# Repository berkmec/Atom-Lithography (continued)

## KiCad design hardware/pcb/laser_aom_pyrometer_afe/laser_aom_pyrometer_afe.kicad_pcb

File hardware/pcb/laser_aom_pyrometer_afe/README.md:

# Laser `80–200 MHz` AOM RF VCA, `10 µs` 2-Color Pyrometer TIA, `1.0 ms` Integrator & `< 0.1 ms` Crowbar PCB

**BOM Coverage:** `S5.5-03`, `S5.5-01`, `S5.5-04`, `S5.3-03` (interfacing `rtl/machine_ctrl/aom_pid_ctrl.v` and `safety_interlock_1oo2d`)  
**Epistemic Status:** `M0/M1_DESIGN_ONLY` — `no_lab_measurement=true`, `no_physical_fab=true`, `iec61508_certified=false`, `semi_s2_certified=false`. All active semiconductors are `{Aday-COTS}` candidate parts.

## 1. Board Summary & Strict KiCad 8 EDA Verification

| Parameter | Value / Measured Result | Requirement / Spec | Status |
| :--- | :--- | :--- | :---: |
| Stackup & Geometry | 4-layer Rogers RO4350B (`ε_r=3.48`, `0.254 mm` outer RF/TIA layers) + Isola FR408HR (`0.800 mm` core), `185 × 125 mm` | 4L Rogers/FR4 mixed-signal PCB | **PASS** |
| Physical Routing & Connectivity | **`63 / 63` multi-pin nets routed (`100%`)**, `835` segments, `221` vias, **`0` unrouted**, **`0` unconnected**, **`0` dangling** | 100% pad-to-pad routed Union-Find DRC | **PASS** |
| Schematic / PCB Netlist | `75` components, `63` nets, `2` closed 3D via-tied `AGND` TIA guard cages (`connect_guard_ring`), `2` `In1/In2` TIA copper keepouts | Strict S-expr + SCH↔PCB parity | **PASS** |
| ERC / DRC Errors | **`0` ERC / `0` DRC** | `0 / 0` | **PASS** |
| Controlled-Impedance `50 Ω` RF Chain (`14` checks) | `Z0 = 50.00 Ω` (`w = 0.5429 mm`, `0.001%` max error across `80–200 MHz` AOM RF path) | `50 Ω ± 5%` | **PASS** |

## 2. Architecture

- **2-Color Fast Pyrometer TIA (`S5.5-03`, `S5.3-03`, `900–1700 K`, `τ_rise ≤ 10 µs`):**
  - InGaAs `1550 nm` (`Hamamatsu G12180-010A`, `OPA657NB`, `R_f = 100 kΩ`, `C_f = 12 pF`) + Si `850 nm` (`Hamamatsu S5971`, `OPA657NB`, `R_f = 200 kΩ`, `C_f = 6.0 pF`) with `F.Cu` guard rings and `In1/In2` copper keepouts feeding dual `ADS8860` 16-bit `1 MS/s` ADCs.
  - Dedicated `TLV3501` hardware over-temperature comparator (`T ≥ 1687 K` Si melt backup) hardwired directly into the local crowbar gate.
- **Inline `1.0 ms` Photodiode Pulse-Energy Integrator (`S5.5-03`):** `Hamamatsu S1223-01` pickoff photodiode → `OPA140` JFET Miller integrator (`C_INT = 100 nF` C0G `±0.5%`, `ADG1211` low-charge-injection reset switch) → `ADS8860` 16-bit ADC + `50 Ω` SMA diagnostic tap.
- **`80–200 MHz` AOM RF VCA Stage (`S5.5-01`, `aom_pid_ctrl.v`):** `AD5541A` 16-bit `100 kHz` SPI DAC + `LT6655B-2.5` ref → `ADA4898-1` VCA driver (`[0.65, 1.40]` gain) → `AD8367` `50 Ω` VCA → `ADG901/HMC547A` `< 15 ns` absorptive RF kill switch → `ADL5602` `50 Ω` output amplifier.
- **`< 0.1 ms` Hardware Crowbar (`S5.5-04`, wired directly to `safety_interlock_1oo2d`):** Dual `ACPL-072L` `< 60 ns` optocouplers (`SAFE_LASER_EN_A`, `SAFE_LASER_EN_B`) in hardware `1oo2` AND gating: (1) `2N7002` VCA zero-clamp, (2) RF kill switch, and (3) series dual-MOSFET `SI2302` `24 V` diode-laser enable cutoff.

## 3. Live `ngspice-47` & Independent MNA Results (`laser_pyro_tia_aom.cir`)

| Metric | `ngspice-47` Measured | Independent Python MNA Ref | Target / Spec | Status |
| :--- | :---: | :---: | :---: | :---: |
| InGaAs `1550 nm` TIA `10–90%` Rise Time | **`2.636 µs`** (`f_-3dB = 132.65 kHz`) | MNA `Z_dc = 99,996.16 Ω` (`0.00004%` diff) | `τ_rise < 10 µs` | **PASS** |
| Si `850 nm` TIA `10–90%` Rise Time | **`2.636 µs`** (`f_-3dB = 132.65 kHz`) | MNA `Z_dc = 199,992.32 Ω` | `τ_rise < 10 µs` | **PASS** |
| `1.0 ms` Pulse-Energy Integrator `2×` Sweep | `1× = 0.999993 V`, `2× = 1.999990 V` (**`0.00001%`** lin err, `0.000 mV` reset) | Ideal `2.00000×` | `< 1.0%` (`±1.5%` BOM) | **PASS** |
| AOM VCA Gain Modulation & RF Flatness | `1.40 / 0.65` ratio **`2.1538`**, `80–200 MHz` flatness **`0.0008 dB`** | Exact `2.15385` | `[0.65, 1.40]`, `< 0.5 dB` | **PASS** |
| Hardware Crowbar Cutoff (`SAFE_LASER_EN_A = 0`) | VCA clamp **`0.273 µs`**, `24 V` Diode-EN **`4.870 µs`** (`23.93 V → 0.12 mV`) | — | `< 50 µs` (`<< 0.1 ms`) | **PASS** |

## 4. Reproducibility

```bash
PYTHONPATH=.:src python -B hardware/pcb/laser_aom_pyrometer_afe/build_laser_aom_pyrometer_afe.py
PYTHONPATH=.:src pytest tests/test_pcb_hv_laser_safety.py -v -p no:cacheprovider
```

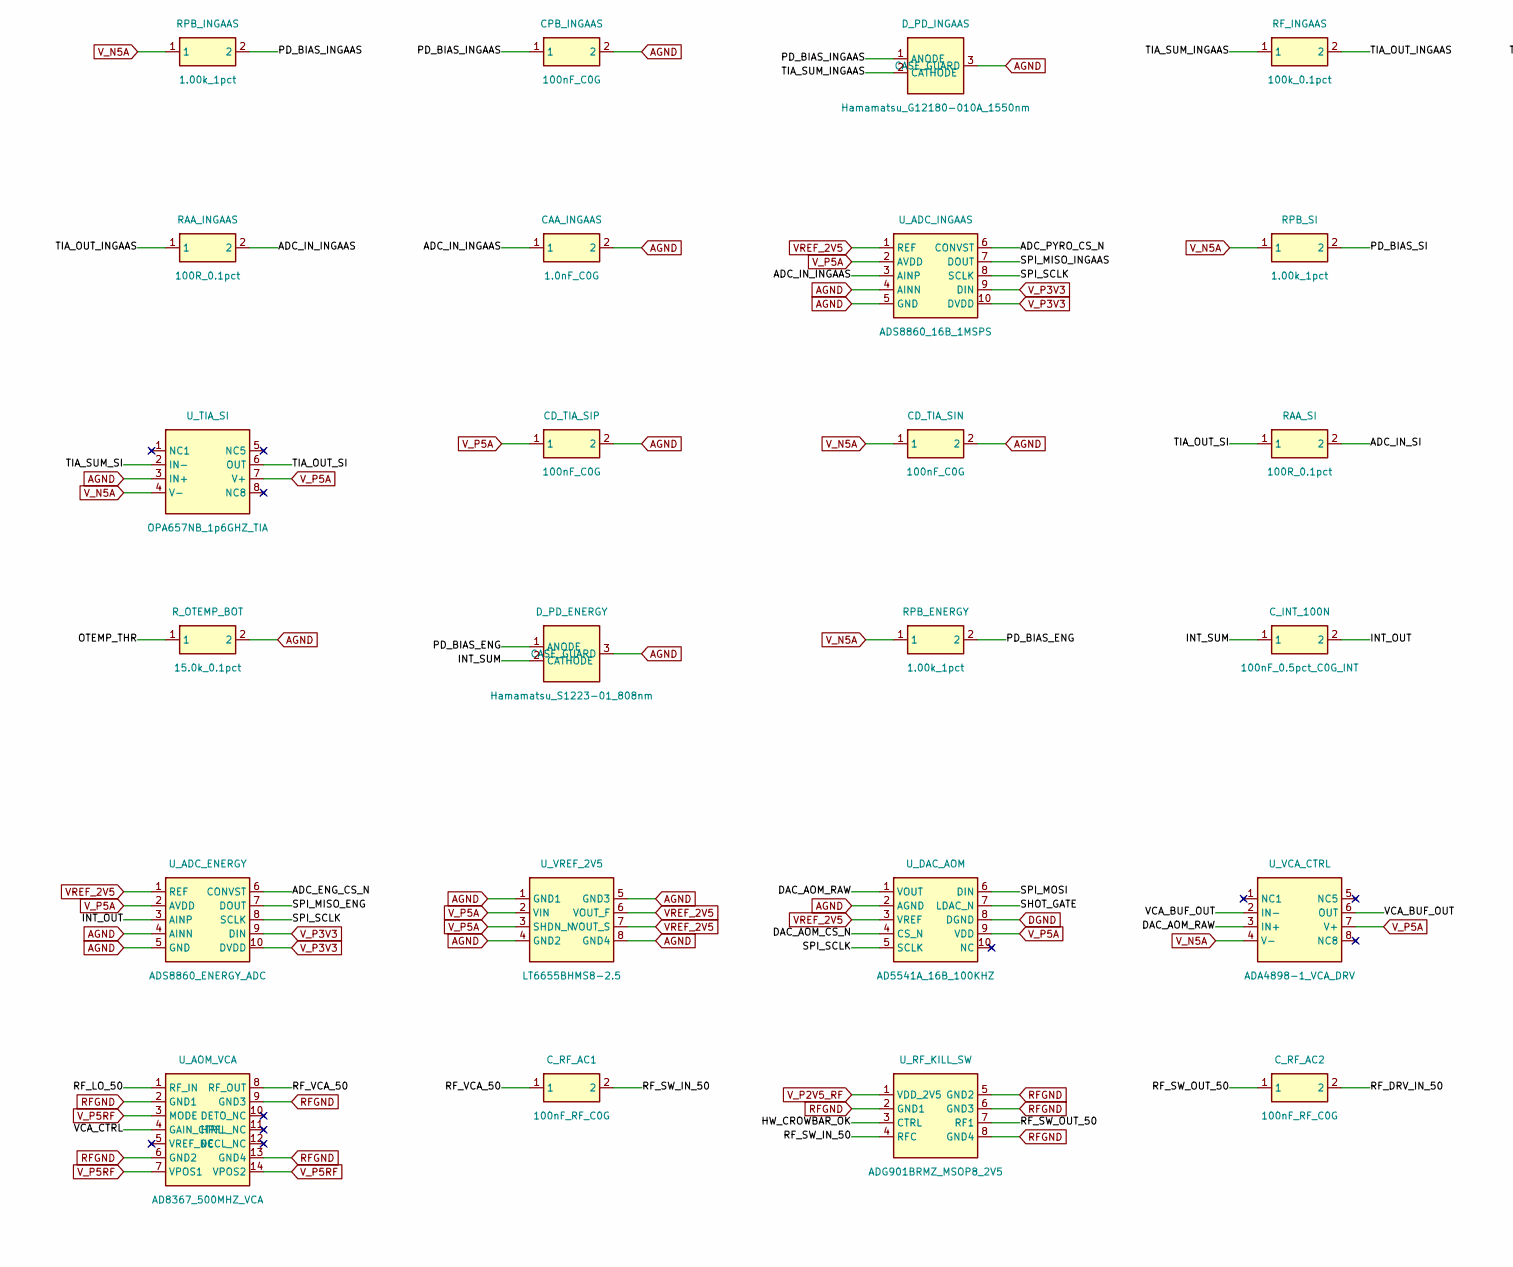
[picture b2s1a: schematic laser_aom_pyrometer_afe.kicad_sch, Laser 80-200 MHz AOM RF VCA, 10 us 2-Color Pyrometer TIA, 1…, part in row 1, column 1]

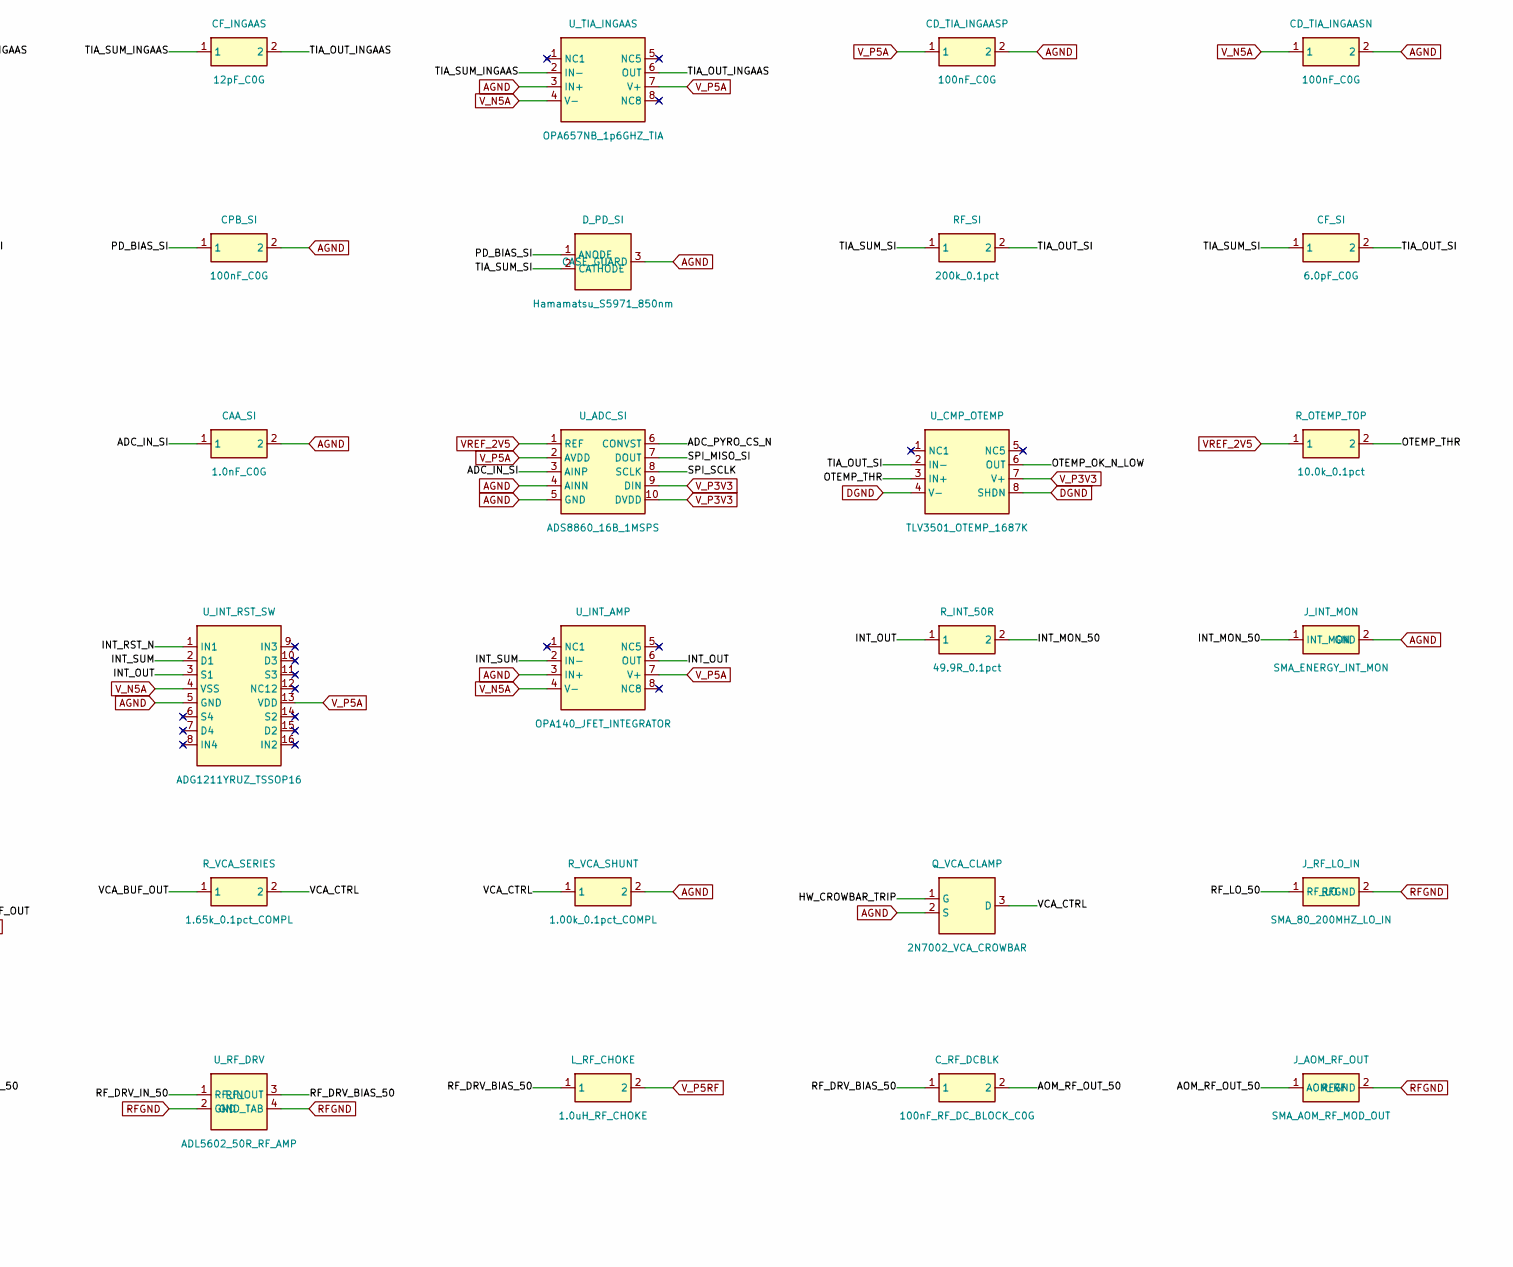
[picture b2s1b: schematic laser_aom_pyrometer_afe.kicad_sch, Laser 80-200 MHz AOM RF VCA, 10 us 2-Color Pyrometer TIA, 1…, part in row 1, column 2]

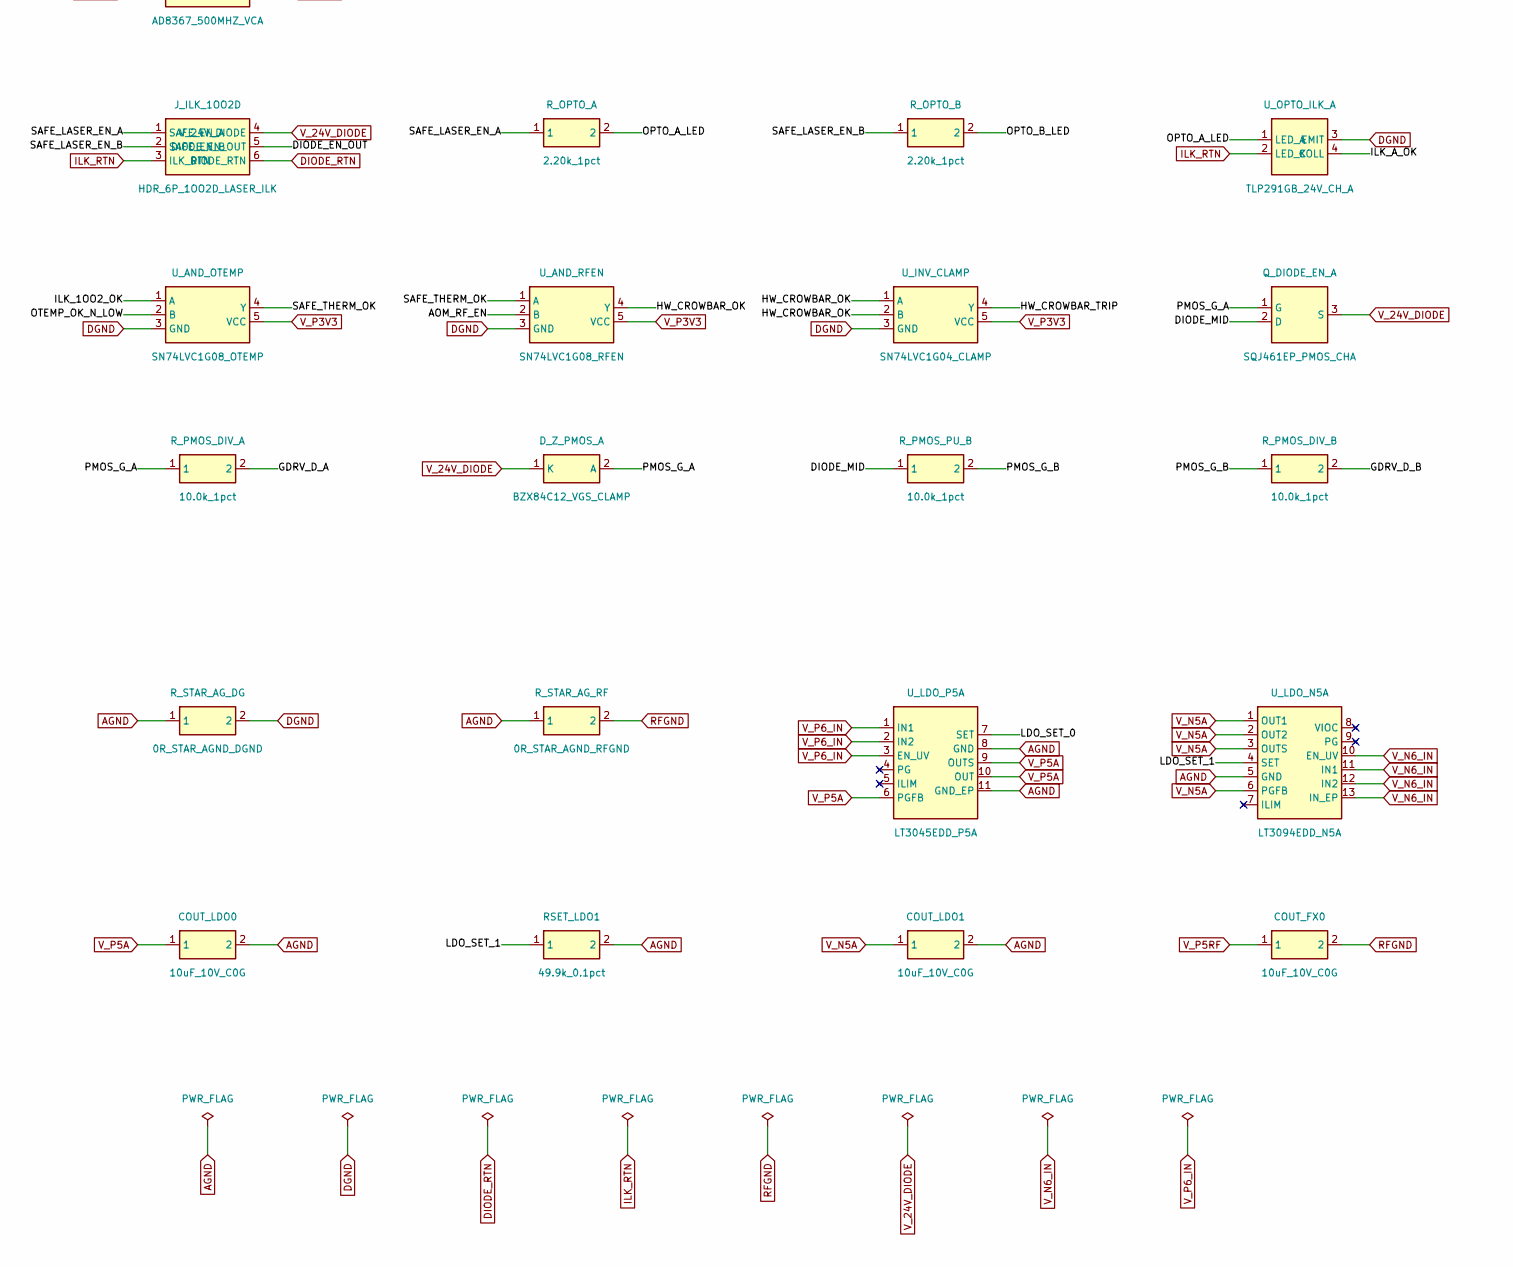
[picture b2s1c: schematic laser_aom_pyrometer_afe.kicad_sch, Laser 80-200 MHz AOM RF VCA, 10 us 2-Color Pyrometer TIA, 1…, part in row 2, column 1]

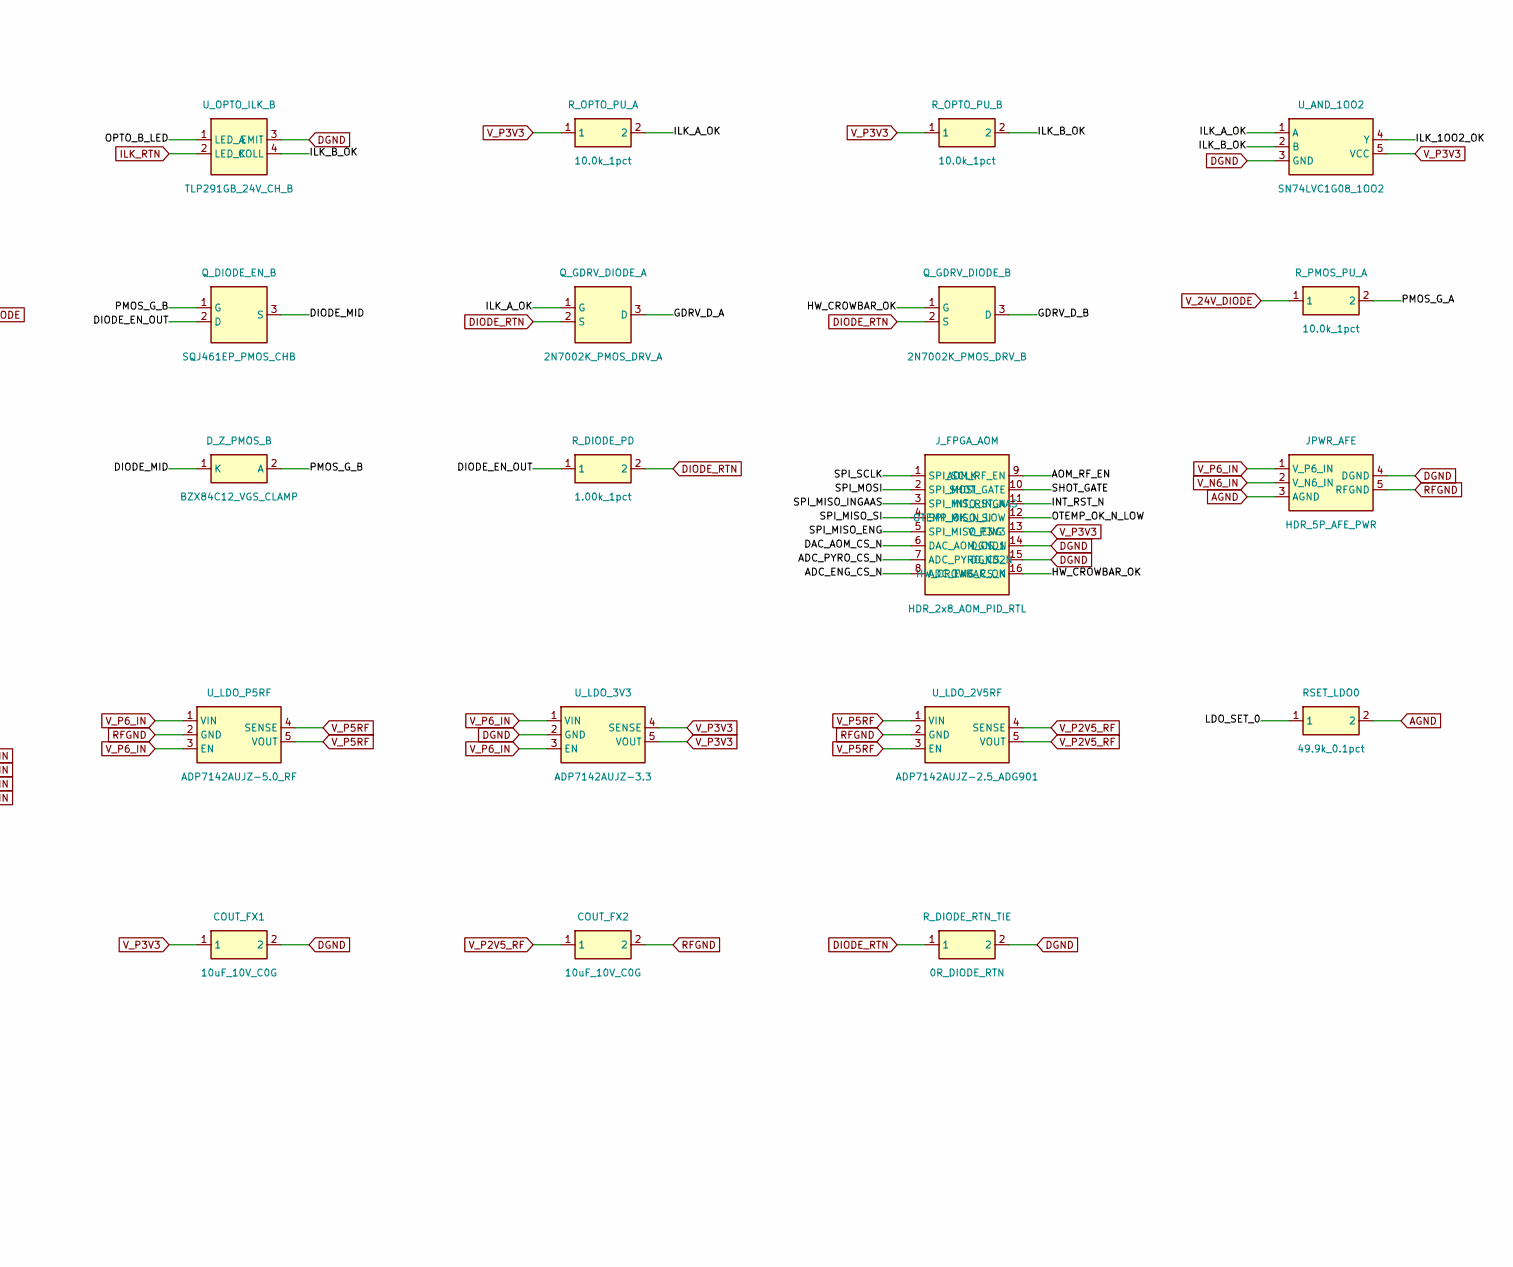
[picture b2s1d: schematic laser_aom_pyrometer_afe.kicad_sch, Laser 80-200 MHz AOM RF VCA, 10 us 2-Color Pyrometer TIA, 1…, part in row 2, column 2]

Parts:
CAA_INGAAS: 1.0nF_C0G; C_0603_1608Metric; MPN 1.0nF_C0G
CAA_SI: 1.0nF_C0G; C_0603_1608Metric; MPN 1.0nF_C0G
CD_TIA_INGAASN: 100nF_C0G; C_0603_1608Metric; MPN 100nF_C0G
CD_TIA_INGAASP: 100nF_C0G; C_0603_1608Metric; MPN 100nF_C0G
CD_TIA_SIN: 100nF_C0G; C_0603_1608Metric; MPN 100nF_C0G
CD_TIA_SIP: 100nF_C0G; C_0603_1608Metric; MPN 100nF_C0G
CF_INGAAS: 12pF_C0G; C_0603_1608Metric; MPN 12pF_C0G
CF_SI: 6.0pF_C0G; C_0603_1608Metric; MPN 6.0pF_C0G
COUT_FX0, COUT_FX1, COUT_FX2: 10uF_10V_C0G; C_0603_1608Metric; MPN 10uF_10V_C0G
COUT_LDO0, COUT_LDO1: 10uF_10V_C0G; C_0603_1608Metric; MPN 10uF_10V_C0G
CPB_INGAAS: 100nF_C0G; C_0603_1608Metric; MPN 100nF_C0G
CPB_SI: 100nF_C0G; C_0603_1608Metric; MPN 100nF_C0G
C_INT_100N: 100nF_0.5pct_C0G_INT; C_1206_3216Metric; MPN TDK_C3216C0G1H104J
C_RF_AC1, C_RF_AC2: 100nF_RF_C0G; C_0603_1608Metric; MPN 100nF_RF_C0G
C_RF_DCBLK: 100nF_RF_DC_BLOCK_C0G; C_0603_1608Metric; MPN 100nF_RF_DC_BLOCK_C0G
D_PD_ENERGY: Hamamatsu_S1223-01_808nm; TO46_PHOTODIODE_3P; MPN Hamamatsu_S1223-01
D_PD_INGAAS: Hamamatsu_G12180-010A_1550nm; TO46_PHOTODIODE_3P; MPN Hamamatsu_G12180-010A_1550nm
D_PD_SI: Hamamatsu_S5971_850nm; TO46_PHOTODIODE_3P; MPN Hamamatsu_S5971_850nm
D_Z_PMOS_A: BZX84C12_VGS_CLAMP; D_0805_2012Metric; MPN BZX84C12_VGS_CLAMP
D_Z_PMOS_B: BZX84C12_VGS_CLAMP; D_0805_2012Metric; MPN BZX84C12_VGS_CLAMP
JPWR_AFE: HDR_5P_AFE_PWR; HDR_1x5_2.54mm; MPN HDR_5P_AFE_PWR
J_AOM_RF_OUT: SMA_AOM_RF_MOD_OUT; SMA_EdgeMount; MPN SMA_AOM_RF_MOD_OUT
J_FPGA_AOM: HDR_2x8_AOM_PID_RTL; HDR_2x8_2.54mm; MPN HDR_2x8_AOM_PID_RTL
J_ILK_1OO2D: HDR_6P_1OO2D_LASER_ILK; HDR_1x6_2.54mm; MPN HDR_6P_1OO2D_LASER_ILK
J_INT_MON: SMA_ENERGY_INT_MON; SMA_EdgeMount; MPN SMA_ENERGY_INT_MON
J_RF_LO_IN: SMA_80_200MHZ_LO_IN; SMA_EdgeMount; MPN SMA_80_200MHZ_LO_IN
L_RF_CHOKE: 1.0uH_RF_CHOKE; L_0805_2012Metric; MPN 1.0uH_RF_CHOKE
Q_DIODE_EN_A: SQJ461EP_PMOS_CHA; TO-252-2; MPN Vishay_SQJ461EP
Q_DIODE_EN_B: SQJ461EP_PMOS_CHB; TO-252-2; MPN Vishay_SQJ461EP
Q_GDRV_DIODE_A: 2N7002K_PMOS_DRV_A; SOT-23; MPN 2N7002K
Q_GDRV_DIODE_B: 2N7002K_PMOS_DRV_B; SOT-23; MPN 2N7002K
Q_VCA_CLAMP: 2N7002_VCA_CROWBAR; SOT-23; MPN 2N7002K
RAA_INGAAS: 100R_0.1pct; R_0603_1608Metric; MPN 100R_0.1pct
RAA_SI: 100R_0.1pct; R_0603_1608Metric; MPN 100R_0.1pct
RF_INGAAS: 100k_0.1pct; R_0603_1608Metric; MPN 100k_0.1pct
RF_SI: 200k_0.1pct; R_0603_1608Metric; MPN 200k_0.1pct
RPB_ENERGY: 1.00k_1pct; R_0603_1608Metric; MPN 1.00k_1pct
RPB_INGAAS: 1.00k_1pct; R_0603_1608Metric; MPN 1.00k_1pct
RPB_SI: 1.00k_1pct; R_0603_1608Metric; MPN 1.00k_1pct
RSET_LDO0, RSET_LDO1: 49.9k_0.1pct; R_0603_1608Metric; MPN 49.9k_0.1pct
R_DIODE_PD: 1.00k_1pct; R_0805_2012Metric; MPN 1.00k_1pct
R_DIODE_RTN_TIE: 0R_DIODE_RTN; R_0603_1608Metric; MPN 0R_DIODE_RTN
R_INT_50R: 49.9R_0.1pct; R_0603_1608Metric; MPN 49.9R_0.1pct
R_OPTO_A: 2.20k_1pct; R_0805_2012Metric; MPN 2.20k_1pct
R_OPTO_B: 2.20k_1pct; R_0805_2012Metric; MPN 2.20k_1pct
R_OPTO_PU_A: 10.0k_1pct; R_0603_1608Metric; MPN 10.0k_1pct
R_OPTO_PU_B: 10.0k_1pct; R_0603_1608Metric; MPN 10.0k_1pct
R_OTEMP_BOT: 15.0k_0.1pct; R_0603_1608Metric; MPN 15.0k_0.1pct
R_OTEMP_TOP: 10.0k_0.1pct; R_0603_1608Metric; MPN 10.0k_0.1pct
R_PMOS_DIV_A: 10.0k_1pct; R_0603_1608Metric; MPN 10.0k_1pct
R_PMOS_DIV_B: 10.0k_1pct; R_0603_1608Metric; MPN 10.0k_1pct
R_PMOS_PU_A: 10.0k_1pct; R_0603_1608Metric; MPN 10.0k_1pct
R_PMOS_PU_B: 10.0k_1pct; R_0603_1608Metric; MPN 10.0k_1pct
R_STAR_AG_DG: 0R_STAR_AGND_DGND; R_0603_1608Metric; MPN 0R_STAR_AGND_DGND
R_STAR_AG_RF: 0R_STAR_AGND_RFGND; R_0603_1608Metric; MPN 0R_STAR_AGND_RFGND
R_VCA_SERIES: 1.65k_0.1pct_COMPL; R_0603_1608Metric; MPN 1.65k_0.1pct_COMPL
R_VCA_SHUNT: 1.00k_0.1pct_COMPL; R_0603_1608Metric; MPN 1.00k_0.1pct_COMPL
U_ADC_ENERGY: ADS8860_ENERGY_ADC; MSOP-10_3x3mm_P0.5mm; MPN ADS8860IDGK
U_ADC_INGAAS: ADS8860_16B_1MSPS; MSOP-10_3x3mm_P0.5mm; MPN ADS8860IDGK
U_ADC_SI: ADS8860_16B_1MSPS; MSOP-10_3x3mm_P0.5mm; MPN ADS8860IDGK
U_AND_1OO2: SN74LVC1G08_1OO2; SOT-23-5; MPN SN74LVC1G08DBVR
U_AND_OTEMP: SN74LVC1G08_OTEMP; SOT-23-5; MPN SN74LVC1G08DBVR
U_AND_RFEN: SN74LVC1G08_RFEN; SOT-23-5; MPN SN74LVC1G08DBVR
U_AOM_VCA: AD8367_500MHZ_VCA; TSSOP-14_4.4x5mm_P0.65mm; MPN AD8367ARUZ
U_CMP_OTEMP: TLV3501_OTEMP_1687K; SOIC-8_3.9x4.9mm_P1.27mm; MPN TLV3501AID
U_DAC_AOM: AD5541A_16B_100KHZ; MSOP-10_3x3mm_P0.5mm; MPN AD5541ABRMZ
U_INT_AMP: OPA140_JFET_INTEGRATOR; SOIC-8_3.9x4.9mm_P1.27mm; MPN OPA140AID
U_INT_RST_SW: ADG1211YRUZ_TSSOP16; TSSOP-16_4.4x5mm_P0.65mm; MPN ADG1211YRUZ
U_INV_CLAMP: SN74LVC1G04_CLAMP; SOT-23-5; MPN SN74LVC1G04DBVR
U_LDO_2V5RF: ADP7142AUJZ-2.5_ADG901; TSOT-23-5; MPN ADP7142AUJZ-2.5
U_LDO_3V3: ADP7142AUJZ-3.3; TSOT-23-5; MPN ADP7142AUJZ-3.3
U_LDO_N5A: LT3094EDD_N5A; DFN-12-1EP_3x3mm_P0.45mm_EP1.65x2.38mm; MPN LT3094EDD
U_LDO_P5A: LT3045EDD_P5A; DFN-10-1EP_3x3mm_P0.5mm_EP1.55x2.48mm; MPN LT3045EDD
U_LDO_P5RF: ADP7142AUJZ-5.0_RF; TSOT-23-5; MPN ADP7142AUJZ-5.0
U_OPTO_ILK_A: TLP291GB_24V_CH_A; SOP-4_3.8x4.1mm_P2.54mm; MPN TLP291GB
U_OPTO_ILK_B: TLP291GB_24V_CH_B; SOP-4_3.8x4.1mm_P2.54mm; MPN TLP291GB
U_RF_DRV: ADL5602_50R_RF_AMP; SOT89_RF_4P; MPN ADL5602ARKZ
U_RF_KILL_SW: ADG901BRMZ_MSOP8_2V5; MSOP-8_3x3mm_P0.65mm; MPN ADG901BRMZ
U_TIA_INGAAS: OPA657NB_1p6GHZ_TIA; SOIC-8_3.9x4.9mm_P1.27mm; MPN OPA657NB
U_TIA_SI: OPA657NB_1p6GHZ_TIA; SOIC-8_3.9x4.9mm_P1.27mm; MPN OPA657NB
U_VCA_CTRL: ADA4898-1_VCA_DRV; SOIC-8_3.9x4.9mm_P1.27mm; MPN ADA4898-1YRDZ
U_VREF_2V5: LT6655BHMS8-2.5; MSOP-8_3x3mm_P0.65mm; MPN LT6655BHMS8-2.5

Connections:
ADC_ENG_CS_N: J_FPGA_AOM.8 (ADC_ENG_CS_N), U_ADC_ENERGY.6 (CONVST)
ADC_IN_INGAAS: CAA_INGAAS.1, RAA_INGAAS.2, U_ADC_INGAAS.3 (AINP)
ADC_IN_SI: CAA_SI.1, RAA_SI.2, U_ADC_SI.3 (AINP)
ADC_PYRO_CS_N: J_FPGA_AOM.7 (ADC_PYRO_CS_N), U_ADC_INGAAS.6 (CONVST), U_ADC_SI.6 (CONVST)
AGND: CAA_INGAAS.2, CAA_SI.2, CD_TIA_INGAASN.2, CD_TIA_INGAASP.2, CD_TIA_SIN.2, CD_TIA_SIP.2, COUT_LDO0.2, COUT_LDO1.2, CPB_INGAAS.2, CPB_SI.2, D_PD_ENERGY.3 (CASE_GUARD), D_PD_INGAAS.3 (CASE_GUARD), D_PD_SI.3 (CASE_GUARD), JPWR_AFE.3 (AGND), J_INT_MON.2 (GND), Q_VCA_CLAMP.2 (S), RSET_LDO0.2, RSET_LDO1.2, R_OTEMP_BOT.2, R_STAR_AG_DG.1, R_STAR_AG_RF.1, R_VCA_SHUNT.2, U_ADC_ENERGY.4 (AINN), U_ADC_ENERGY.5 (GND), U_ADC_INGAAS.4 (AINN), U_ADC_INGAAS.5 (GND), U_ADC_SI.4 (AINN), U_ADC_SI.5 (GND), U_DAC_AOM.2 (AGND), U_INT_AMP.3 (IN+), U_INT_RST_SW.5 (GND), U_LDO_N5A.5 (GND), U_LDO_P5A.8 (GND), U_LDO_P5A.11 (GND_EP), U_TIA_INGAAS.3 (IN+), U_TIA_SI.3 (IN+), U_VREF_2V5.1 (GND1), U_VREF_2V5.4 (GND2), U_VREF_2V5.5 (GND3), U_VREF_2V5.8 (GND4)
AOM_RF_EN: J_FPGA_AOM.9 (AOM_RF_EN), U_AND_RFEN.2 (B)
AOM_RF_OUT_50: C_RF_DCBLK.2, J_AOM_RF_OUT.1 (AOM_RF)
DAC_AOM_CS_N: J_FPGA_AOM.6 (DAC_AOM_CS_N), U_DAC_AOM.4 (CS_N)
DAC_AOM_RAW: U_DAC_AOM.1 (VOUT), U_VCA_CTRL.3 (IN+)
DGND: COUT_FX1.2, JPWR_AFE.4 (DGND), J_FPGA_AOM.14 (DGND1), J_FPGA_AOM.15 (DGND2), R_DIODE_RTN_TIE.2, R_STAR_AG_DG.2, U_AND_1OO2.3 (GND), U_AND_OTEMP.3 (GND), U_AND_RFEN.3 (GND), U_CMP_OTEMP.4 (V-), U_CMP_OTEMP.8 (SHDN), U_DAC_AOM.8 (DGND), U_INV_CLAMP.3 (GND), U_LDO_3V3.2 (GND), U_OPTO_ILK_A.3 (EMIT), U_OPTO_ILK_B.3 (EMIT)
DIODE_EN_OUT: J_ILK_1OO2D.5 (DIODE_EN_OUT), Q_DIODE_EN_B.2 (D), R_DIODE_PD.1
DIODE_MID: D_Z_PMOS_B.1 (K), Q_DIODE_EN_A.2 (D), Q_DIODE_EN_B.3 (S), R_PMOS_PU_B.1
DIODE_RTN: J_ILK_1OO2D.6 (DIODE_RTN), Q_GDRV_DIODE_A.2 (S), Q_GDRV_DIODE_B.2 (S), R_DIODE_PD.2, R_DIODE_RTN_TIE.1
GDRV_D_A: Q_GDRV_DIODE_A.3 (D), R_PMOS_DIV_A.2
GDRV_D_B: Q_GDRV_DIODE_B.3 (D), R_PMOS_DIV_B.2
HW_CROWBAR_OK: J_FPGA_AOM.16 (HW_CROWBAR_OK), Q_GDRV_DIODE_B.1 (G), U_AND_RFEN.4 (Y), U_INV_CLAMP.1 (A), U_INV_CLAMP.2 (B), U_RF_KILL_SW.3 (CTRL)
HW_CROWBAR_TRIP: Q_VCA_CLAMP.1 (G), U_INV_CLAMP.4 (Y)
ILK_1OO2_OK: U_AND_1OO2.4 (Y), U_AND_OTEMP.1 (A)
ILK_A_OK: Q_GDRV_DIODE_A.1 (G), R_OPTO_PU_A.2, U_AND_1OO2.1 (A), U_OPTO_ILK_A.4 (COLL)
ILK_B_OK: R_OPTO_PU_B.2, U_AND_1OO2.2 (B), U_OPTO_ILK_B.4 (COLL)
ILK_RTN: J_ILK_1OO2D.3 (ILK_RTN), U_OPTO_ILK_A.2 (LED_K), U_OPTO_ILK_B.2 (LED_K)
INT_MON_50: J_INT_MON.1 (INT_MON), R_INT_50R.2
INT_OUT: C_INT_100N.2, R_INT_50R.1, U_ADC_ENERGY.3 (AINP), U_INT_AMP.6 (OUT), U_INT_RST_SW.3 (S1)
INT_RST_N: J_FPGA_AOM.11 (INT_RST_N), U_INT_RST_SW.1 (IN1)
INT_SUM: C_INT_100N.1, D_PD_ENERGY.2 (CATHODE), U_INT_AMP.2 (IN-), U_INT_RST_SW.2 (D1)
LDO_SET_0: RSET_LDO0.1, U_LDO_P5A.7 (SET)
LDO_SET_1: RSET_LDO1.1, U_LDO_N5A.4 (SET)
OPTO_A_LED: R_OPTO_A.2, U_OPTO_ILK_A.1 (LED_A)
OPTO_B_LED: R_OPTO_B.2, U_OPTO_ILK_B.1 (LED_A)
OTEMP_OK_N_LOW: J_FPGA_AOM.12 (OTEMP_OK_N_LOW), U_AND_OTEMP.2 (B), U_CMP_OTEMP.6 (OUT)
OTEMP_THR: R_OTEMP_BOT.1, R_OTEMP_TOP.2, U_CMP_OTEMP.3 (IN+)
PD_BIAS_ENG: D_PD_ENERGY.1 (ANODE), RPB_ENERGY.2
PD_BIAS_INGAAS: CPB_INGAAS.1, D_PD_INGAAS.1 (ANODE), RPB_INGAAS.2
PD_BIAS_SI: CPB_SI.1, D_PD_SI.1 (ANODE), RPB_SI.2
PMOS_G_A: D_Z_PMOS_A.2 (A), Q_DIODE_EN_A.1 (G), R_PMOS_DIV_A.1, R_PMOS_PU_A.2
PMOS_G_B: D_Z_PMOS_B.2 (A), Q_DIODE_EN_B.1 (G), R_PMOS_DIV_B.1, R_PMOS_PU_B.2
RFGND: COUT_FX0.2, COUT_FX2.2, JPWR_AFE.5 (RFGND), J_AOM_RF_OUT.2 (RFGND), J_RF_LO_IN.2 (RFGND), R_STAR_AG_RF.2, U_AOM_VCA.2 (GND1), U_AOM_VCA.6 (GND2), U_AOM_VCA.9 (GND3), U_AOM_VCA.13 (GND4), U_LDO_2V5RF.2 (GND), U_LDO_P5RF.2 (GND), U_RF_DRV.2 (GND), U_RF_DRV.4 (GND_TAB), U_RF_KILL_SW.2 (GND1), U_RF_KILL_SW.5 (GND2), U_RF_KILL_SW.6 (GND3), U_RF_KILL_SW.8 (GND4)
RF_DRV_BIAS_50: C_RF_DCBLK.1, L_RF_CHOKE.1, U_RF_DRV.3 (RF_OUT)
RF_DRV_IN_50: C_RF_AC2.2, U_RF_DRV.1 (RF_IN)
RF_LO_50: J_RF_LO_IN.1 (RF_LO), U_AOM_VCA.1 (RF_IN)
RF_SW_IN_50: C_RF_AC1.2, U_RF_KILL_SW.4 (RFC)
RF_SW_OUT_50: C_RF_AC2.1, U_RF_KILL_SW.7 (RF1)
RF_VCA_50: C_RF_AC1.1, U_AOM_VCA.8 (RF_OUT)
SAFE_LASER_EN_A: J_ILK_1OO2D.1 (SAFE_EN_A), R_OPTO_A.1
SAFE_LASER_EN_B: J_ILK_1OO2D.2 (SAFE_EN_B), R_OPTO_B.1
SAFE_THERM_OK: U_AND_OTEMP.4 (Y), U_AND_RFEN.1 (A)
SHOT_GATE: J_FPGA_AOM.10 (SHOT_GATE), U_DAC_AOM.7 (LDAC_N)
SPI_MISO_ENG: J_FPGA_AOM.5 (SPI_MISO_ENG), U_ADC_ENERGY.7 (DOUT)
SPI_MISO_INGAAS: J_FPGA_AOM.3 (SPI_MISO_INGAAS), U_ADC_INGAAS.7 (DOUT)
SPI_MISO_SI: J_FPGA_AOM.4 (SPI_MISO_SI), U_ADC_SI.7 (DOUT)
SPI_MOSI: J_FPGA_AOM.2 (SPI_MOSI), U_DAC_AOM.6 (DIN)
SPI_SCLK: J_FPGA_AOM.1 (SPI_SCLK), U_ADC_ENERGY.8 (SCLK), U_ADC_INGAAS.8 (SCLK), U_ADC_SI.8 (SCLK), U_DAC_AOM.5 (SCLK)
TIA_OUT_INGAAS: CF_INGAAS.2, RAA_INGAAS.1, RF_INGAAS.2, U_TIA_INGAAS.6 (OUT)
TIA_OUT_SI: CF_SI.2, RAA_SI.1, RF_SI.2, U_CMP_OTEMP.2 (IN-), U_TIA_SI.6 (OUT)
TIA_SUM_INGAAS: CF_INGAAS.1, D_PD_INGAAS.2 (CATHODE), RF_INGAAS.1, U_TIA_INGAAS.2 (IN-)
TIA_SUM_SI: CF_SI.1, D_PD_SI.2 (CATHODE), RF_SI.1, U_TIA_SI.2 (IN-)
VCA_BUF_OUT: R_VCA_SERIES.1, U_VCA_CTRL.2 (IN-), U_VCA_CTRL.6 (OUT)
VCA_CTRL: Q_VCA_CLAMP.3 (D), R_VCA_SERIES.2, R_VCA_SHUNT.1, U_AOM_VCA.4 (GAIN_CTRL)
VREF_2V5: R_OTEMP_TOP.1, U_ADC_ENERGY.1 (REF), U_ADC_INGAAS.1 (REF), U_ADC_SI.1 (REF), U_DAC_AOM.3 (VREF), U_VREF_2V5.6 (VOUT_F), U_VREF_2V5.7 (VOUT_S)
V_24V_DIODE: D_Z_PMOS_A.1 (K), J_ILK_1OO2D.4 (V_24V_DIODE), Q_DIODE_EN_A.3 (S), R_PMOS_PU_A.1
V_N5A: CD_TIA_INGAASN.1, CD_TIA_SIN.1, COUT_LDO1.1, RPB_ENERGY.1, RPB_INGAAS.1, RPB_SI.1, U_INT_AMP.4 (V-), U_INT_RST_SW.4 (VSS), U_LDO_N5A.1 (OUT1), U_LDO_N5A.2 (OUT2), U_LDO_N5A.3 (OUTS), U_LDO_N5A.6 (PGFB), U_TIA_INGAAS.4 (V-), U_TIA_SI.4 (V-), U_VCA_CTRL.4 (V-)
V_N6_IN: JPWR_AFE.2 (V_N6_IN), U_LDO_N5A.10 (EN_UV), U_LDO_N5A.11 (IN1), U_LDO_N5A.12 (IN2), U_LDO_N5A.13 (IN_EP)
V_P2V5_RF: COUT_FX2.1, U_LDO_2V5RF.4 (SENSE), U_LDO_2V5RF.5 (VOUT), U_RF_KILL_SW.1 (VDD_2V5)
V_P3V3: COUT_FX1.1, J_FPGA_AOM.13 (V_P3V3), R_OPTO_PU_A.1, R_OPTO_PU_B.1, U_ADC_ENERGY.9 (DIN), U_ADC_ENERGY.10 (DVDD), U_ADC_INGAAS.9 (DIN), U_ADC_INGAAS.10 (DVDD), U_ADC_SI.9 (DIN), U_ADC_SI.10 (DVDD), U_AND_1OO2.5 (VCC), U_AND_OTEMP.5 (VCC), U_AND_RFEN.5 (VCC), U_CMP_OTEMP.7 (V+), U_INV_CLAMP.5 (VCC), U_LDO_3V3.4 (SENSE), U_LDO_3V3.5 (VOUT)
V_P5A: CD_TIA_INGAASP.1, CD_TIA_SIP.1, COUT_LDO0.1, U_ADC_ENERGY.2 (AVDD), U_ADC_INGAAS.2 (AVDD), U_ADC_SI.2 (AVDD), U_DAC_AOM.9 (VDD), U_INT_AMP.7 (V+), U_INT_RST_SW.13 (VDD), U_LDO_P5A.6 (PGFB), U_LDO_P5A.9 (OUTS), U_LDO_P5A.10 (OUT), U_TIA_INGAAS.7 (V+), U_TIA_SI.7 (V+), U_VCA_CTRL.7 (V+), U_VREF_2V5.2 (VIN), U_VREF_2V5.3 (SHDN_N)
V_P5RF: COUT_FX0.1, L_RF_CHOKE.2, U_AOM_VCA.3 (MODE), U_AOM_VCA.7 (VPOS1), U_AOM_VCA.14 (VPOS2), U_LDO_2V5RF.1 (VIN), U_LDO_2V5RF.3 (EN), U_LDO_P5RF.4 (SENSE), U_LDO_P5RF.5 (VOUT)
V_P6_IN: JPWR_AFE.1 (V_P6_IN), U_LDO_3V3.1 (VIN), U_LDO_3V3.3 (EN), U_LDO_P5A.1 (IN1), U_LDO_P5A.2 (IN2), U_LDO_P5A.3 (EN_UV), U_LDO_P5RF.1 (VIN), U_LDO_P5RF.3 (EN)

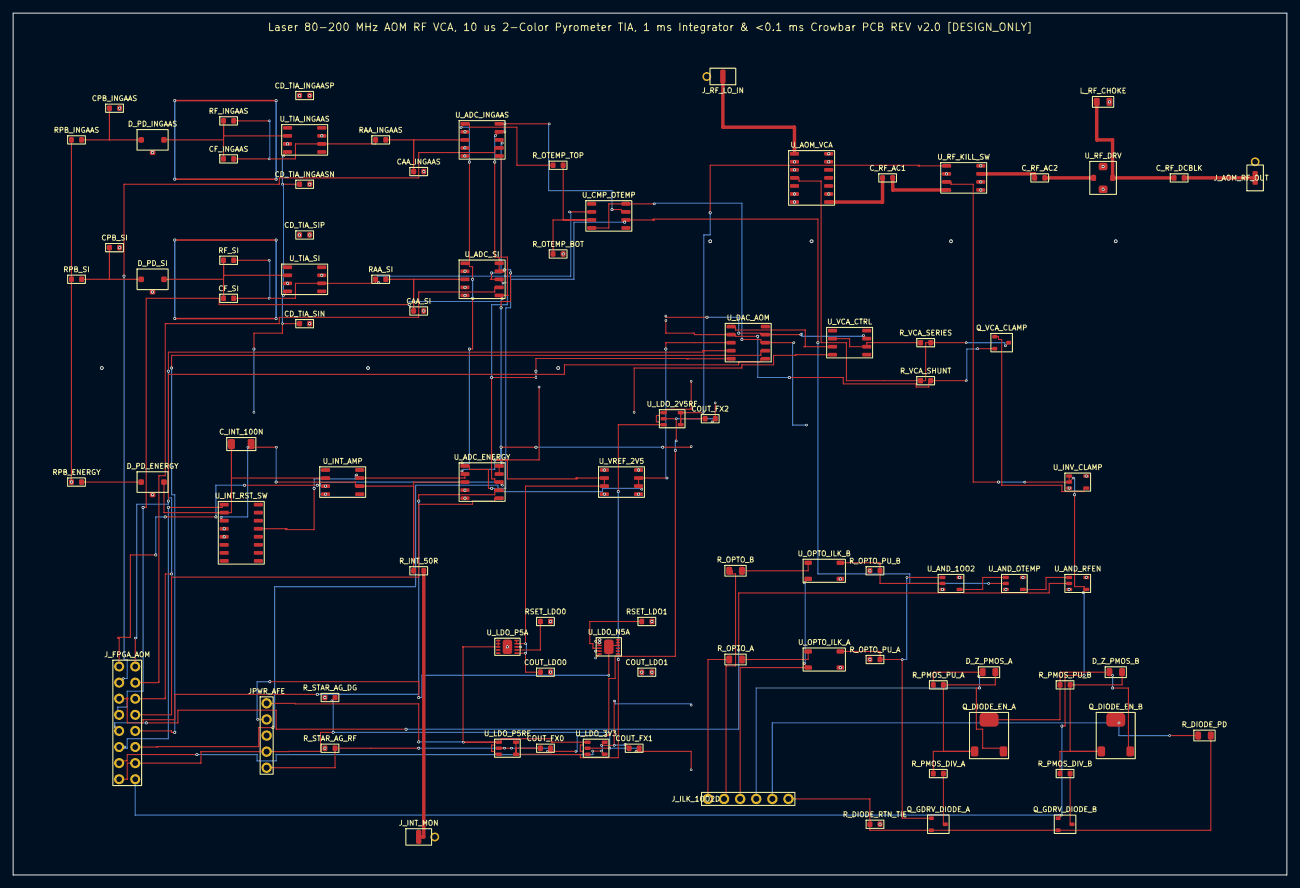
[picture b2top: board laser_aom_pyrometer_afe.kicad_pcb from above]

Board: 4 copper layers, 201.0 x 136.0 mm, 87 parts (0 on the bottom side), 67 nets.
